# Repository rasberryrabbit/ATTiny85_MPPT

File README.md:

# ATTiny85
Solar MPPT circuit.
Fianally working first firmware, but it need more testing.
Button is calibrate op-amp offset voltage at no load. It stored EEPROM.

Coding by Arduino 1.8.7 / ATTinycore.
~Algorithm convert from old MPPT code of mine.~
It implement new simple algorithm that work well with high solar output.
~But it have low power output under low solar output condition(stuck in high voltage).~
It has no PWM noise at high load.(hopely)
It has 8KHz switching frequency.
It works better than old 16f676 or 12f675 version due to no PWM noise.

11 milli-ohm N-ch logic level FET(BUK9511) used for current sensor. 
It can replace by 11 mili-ohm or higher Rds-on(<40 milli) resistance logic level FET.

BUK9511-55A -> BUK9508-55A
Transistor 2N2222A -> BC547 or compatible
Transistor 2N2907A -> BC557 or compatible

L1 100~330uH

LM358N can replace by other pin-compatible regular OP-AMP.

D8-D9 used for 3.6v Reference. Each has about 1.8v voltage drop.

Q1 gate voltage is 3.6v. It's depend on FET specification.

Q1, Q2 can skip heat spreader with low POWER Solar panel. No heat with 10W panel.

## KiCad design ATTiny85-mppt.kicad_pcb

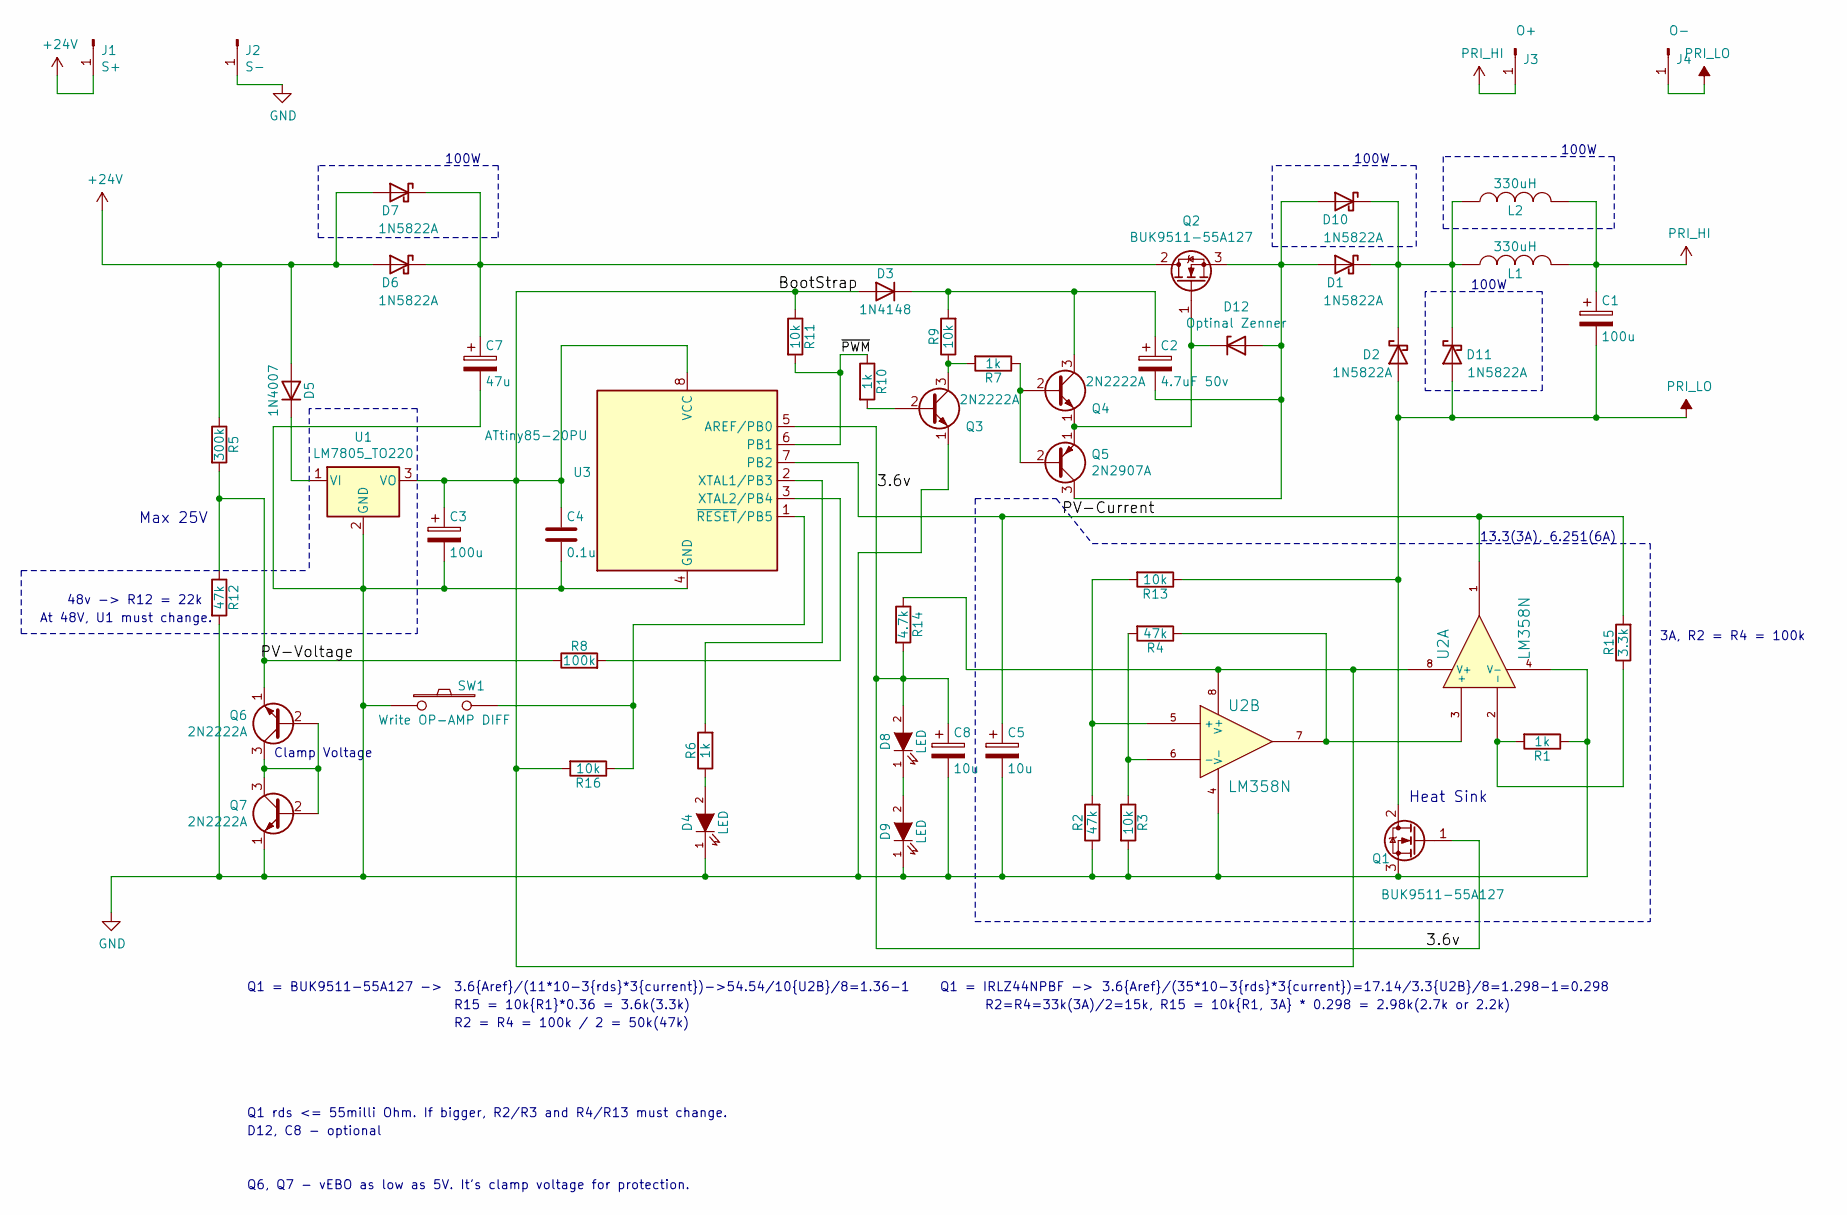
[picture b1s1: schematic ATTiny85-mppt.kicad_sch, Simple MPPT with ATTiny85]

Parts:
C1, C3: 100u; CP_Radial_D12.5mm_P5.00mm
C2: 4.7uF 50v; CP_Radial_D12.5mm_P5.00mm
C4: 0.1u; C_Disc_D12.5mm_W5.0mm_P7.50mm
C5, C8: 10u; CP_Radial_D12.5mm_P5.00mm
C7: 47u; CP_Radial_D12.5mm_P5.00mm
D1, D2, D6, D7, D10, D11: 1N5822A; D_DO-201AD_P15.24mm_Horizontal
D3: 1N4148; D_DO-41_SOD81_P10.16mm_Horizontal
D4, D8, D9: LED; LED_D4.0mm
D5: 1N4007; D_DO-41_SOD81_P10.16mm_Horizontal
D12: Optinal Zenner; D_DO-41_SOD81_P10.16mm_Horizontal
J1: S+; 1pin
J2: S-; 1pin
J3: O+; 1pin
J4: O-; 1pin
L1, L2: 330uH; L_Toroid_Vertical_L33.0mm_W17.8mm_P12.70mm_Pulse_KM-5
Q1, Q2: BUK9511-55A127; TO-220_Neutral123_Vertical
Q3, Q4, Q6, Q7: 2N2222A; TO-92_Inline_Wide
Q5: 2N2907A; TO-92_Inline_Wide
R1, R6, R7, R10: 1k; R_Axial_DIN0309_L9.0mm_D3.2mm_P12.70mm_Horizontal
R2, R4, R12: 47k; R_Axial_DIN0309_L9.0mm_D3.2mm_P12.70mm_Horizontal
R3, R9, R11, R13, R16: 10k; R_Axial_DIN0309_L9.0mm_D3.2mm_P12.70mm_Horizontal
R5: 300k; R_Axial_DIN0309_L9.0mm_D3.2mm_P12.70mm_Horizontal
R8: 100k; R_Axial_DIN0309_L9.0mm_D3.2mm_P12.70mm_Horizontal
R14: 4.7k; R_Axial_DIN0309_L9.0mm_D3.2mm_P12.70mm_Horizontal
R15: 3.3k; R_Axial_DIN0309_L9.0mm_D3.2mm_P12.70mm_Horizontal
SW1: Write OP-AMP DIFF; SW_PUSH_6mm
U1: LM7805_TO220; TO-220-3_Vertical
U2: LM358N; DIP-8_W7.62mm
U3: ATtiny85-20PU; DIP-8_W7.62mm

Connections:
+24V: D5.2 (A), D6.2 (A), D7.2 (A), J1.1, R5.1; also elsewhere on the board
/3.6v: C8.1, D8.2 (A), Q1.1 (G), R14.2, U3.5 (AREF/PB0)
/BootStrap: C3.1, C4.1, D3.2 (A), R11.1, R14.1, R16.2, U1.3 (VO), U2.8 (V+), U3.8 (VCC)
/PV-Current: C5.1, R15.2, U2.1, U3.7 (PB2)
/PV-Voltage: Q6.1 (E), R5.2, R8.1, R12.1
/~PWM: R10.1, R11.2, U3.6 (PB1)
GND: C3.2, C4.2, C5.2, C7.2, C8.2, D4.1 (K), D9.1 (K), J2.1, Q1.3 (S), Q3.1 (E), Q7.1 (E), R1.1, R2.1, R3.2, R12.2, SW1.1, U1.2 (GND), U2.4 (V-), U3.4 (GND); also elsewhere on the board
unnamed: C2.1, D3.1 (K), Q4.3 (C), R9.2
unnamed: C2.2, D1.2 (A), D10.2 (A), D12.2 (A), Q2.3 (S), Q5.3 (C)
unnamed: C7.1, D6.1 (K), D7.1 (K), Q2.2 (D)
unnamed: D1.1 (K), D2.1 (K), D10.1 (K), D11.1 (K), L1.1, L2.1
unnamed: D4.2 (A), R6.1
unnamed: D5.1 (K), U1.1 (VI)
unnamed: D8.1 (K), D9.2 (A)
unnamed: D12.1 (K), Q2.1 (G), Q4.1 (E), Q5.1 (E)
unnamed: Q3.2 (B), R10.2
unnamed: Q3.3 (C), R7.2, R9.1
unnamed: Q4.2 (B), Q5.2 (B), R7.1
unnamed: Q6.2 (B), Q6.3 (C), Q7.2 (B), Q7.3 (C)
unnamed: R1.2, R15.1, U2.2 (-)
unnamed: R3.1, R4.2, U2.6 (-)
unnamed: R4.1, U2.3 (+), U2.7
unnamed: R6.2, U3.2 (XTAL1/PB3)
unnamed: R8.2, U3.3 (XTAL2/PB4)
unnamed: R2.2, R13.2, U2.5 (+)
unnamed 25: R16.1, SW1.2, U3.1 (~RESET/PB5); also elsewhere on the board
PRI_HI: C1.1, J3.1, L1.2, L2.2; also elsewhere on the board
PRI_LO: C1.2, D2.2 (A), D11.2 (A), J4.1, Q1.2 (D), R13.1; also elsewhere on the board

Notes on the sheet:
3A, R2 = R4 = 100k
48v -> R12 = 22k
100W
3.6{Aref}/(11*10-3{rds}*3{current})->54.54/10{U2B}/8=1.36-1
Clamp Voltage
R2 = R4 = 100k / 2 = 50k(47k)
Heat Sink
D12, C8 - optional
Max 25V
At 48V, U1 must change.
13.3(3A), 6.251(6A)
Q1 = BUK9511-55A127 ->
Q1 rds <= 55milli Ohm. If bigger, R2/R3 and R4/R13 must change.
Q6, Q7 - vEBO as low as 5V. It's clamp voltage for protection.
R2=R4=33k(3A)/2=15k, R15 = 10k{R1, 3A} * 0.298 = 2.98k(2.7k or 2.2k)
Q1 = IRLZ44NPBF ->
R15 = 10k{R1}*0.36 = 3.6k(3.3k)
3.6{Aref}/(35*10-3{rds}*3{current})=17.14/3.3{U2B}/8=1.298-1=0.298

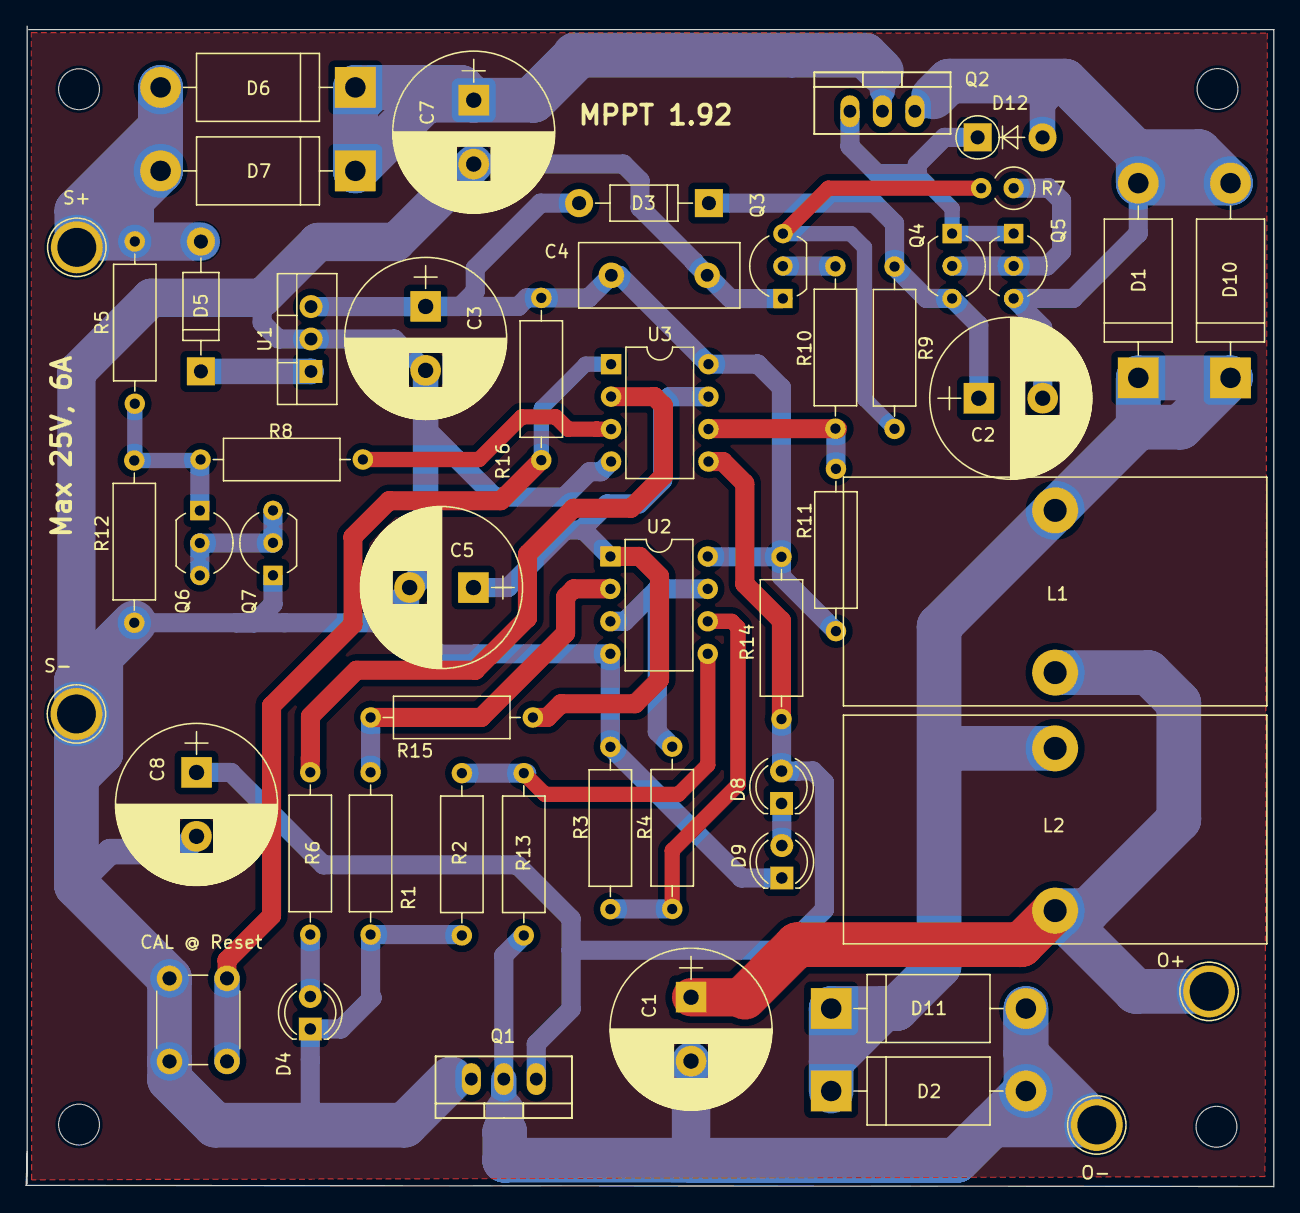
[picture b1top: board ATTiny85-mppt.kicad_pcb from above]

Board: 2 copper layers, 97.6 x 90.8 mm, 52 parts (0 on the bottom side), 28 nets.

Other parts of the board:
CAL @ Reset: Write OP-AMP DIFF; SW_PUSH_6mm
O+: O+; 1pin
O-: O-; 1pin
S+: S+; 1pin
S-: S-; 1pin

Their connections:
+24V: S+.1; also elsewhere on the board
GND: CAL @ Reset.1, S-.1; also elsewhere on the board
unnamed 25: CAL @ Reset.2; also elsewhere on the board
PRI_HI: O+.1; also elsewhere on the board
PRI_LO: O-.1; also elsewhere on the board

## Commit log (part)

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2018-10-21 First.
2018-10-21 update comment.
2018-10-24 fix pin mode on PWM.
2018-10-24 Fix pin Names. Fix delay values for 1MHz clock. Diable OCAL(OP-AMP Calibration) to default.
2018-10-24 Fix some settings.
2018-10-24 minor.
2018-10-24 Put some delays at start.
2018-10-25 Add hint for alternative FET IRLZ44.
2018-10-25 Add formula for OP-AMP Current Detector Value.
2018-10-26 Clarify alternative FET part number.
2018-10-26 Update more reliable value for FET IRLZ44N.
2018-10-28 fix OP-AMP formula.
2018-10-28 Update comment for bigger rds FET.
2018-10-30 Fix circuit - FET Bootstrap don't work. Fix code - Inverting mode PWM.
2018-10-30 fix typecast.
2018-10-30 remove stuck condition.
2018-10-30 Back to non-inverting. Fix FET Bootstrap.
2018-10-31 Fix by Invert Mode, 8Khz PWM. FET Bootstrap don't work with Higher frequency.
2018-10-31 Update PCB Layout.
2018-10-31 Update.
2018-10-31 Down PWM clock to 4KHz. ADC check test
2018-10-31 Fix _AnalogRead function.
2018-11-01 Fix ADC reference parameter. Fix OP-AMP Offset at first.
2018-11-01 fix FET bootstrap capacitor.
2018-11-01 update. but still don't work.
2018-11-01 Lower Max PWM.
2018-11-02 Add another P FET for switching.
2018-11-02 Refine code.
2018-11-02 add stall check. fix resetting parameters.
2018-11-02 miss one;
2018-11-03 Fix low voltage condition
2018-11-03 fix conditions.
2018-11-03 another condition.
2018-11-04 fix stall at low voltage.
2018-11-08 New method. WIP
2018-11-10 Add AREF capacitor.
2018-11-13 First working firmware. It need more testing.
2018-11-13 remove some component.
2018-11-13 regenerate pcb files.
2018-11-15 update readme.
2018-11-15 Increase ADC checking loop count.
2018-11-15 update bootstrap capacitor.
2018-11-17 update PCB file. update capacitor and add resistor.
2018-11-17 fix Q5 value.
2018-11-17 change bootstrap diode.
2018-11-18 clarify diode value.
2018-11-18 refine pcb layout.
2018-11-18 rearrnage some lines.
2018-11-18 rearrange.
2018-11-18 rearrange lines.
2018-11-19 lower adc loop.
2018-11-19 back to old adc loop.
2018-11-19 Don't be over optimal power voltage.
2018-11-20 update delay definitions.
2018-11-20 update delay constant. It may affect by ripple.
2018-11-20 upload image.
2018-11-22 Change update interval under current condition.
2018-11-22 Change min max PWM and test.
2018-11-23 update condition.
2018-11-23 update interval on low current.
2018-11-23 fix.
2018-11-24 stablize PWM.
2018-11-24 remove useless function and 8kHz PWM clock.
2018-11-25 add watchdog.
2018-11-25 add low current limit.
2018-11-25 check watchdog reset condition.
2018-11-25 R11 to 4.7k
2018-11-25 remove low current condition.
2018-11-26 avoid low voltage condition.
2018-11-27 fix led delay.
2018-11-27 sync adc reading.
2018-11-27 use non-interrupt handler for sync
2018-11-28 improve adc routine
2018-11-28 reduce adc loop.
2018-11-29 Remove R11. It is a lot lower current sensing voltage.
2018-11-29 Remove R11 on PCB layout.
2018-11-29 reduce update delay.
2018-11-30 Test adc sample times.
2018-11-30 disable edge detection. lower update delay.
2018-11-30 update PCB.
2018-11-30 update circuit.
2018-12-07 update C2 value. 10uF is also good.
2018-12-12 increase update interval. change ADC read order.
2018-12-13 fix current ADC reading. need more testing.
2018-12-13 set more optimized update interval.
2018-12-14 C6 to optional component.
2018-12-14 typecast on power multiple calc.
2018-12-15 Low voltage-High current stuck solved by removing C6. More testing.
2018-12-15 Reduce latency. It works on value 10.
2018-12-17 Remove C6
2018-12-17 Describe arduino tool option.
2018-12-18 Add alternative FET.
2018-12-20 R15 -> 4.7k. Current sensing is more higher than expected. 62mA -> 67mV.
2018-12-21 refine OP-AMP resistor formula. but it still same with first design(+10mV). it may safe under 3A current.
2018-12-22 update resistor formula.
2018-12-23 add note for R15.
2018-12-26 Add voltage clamp.
2019-01-07 fix low voltage(<2.7V) PLL lockup condition.
2019-01-22 another fix for low vcc stall.
2019-01-22 add delay time for PLL.
2019-01-31 Create LICENSE
2019-02-03 update watchdog init code.
2019-02-03 Change init order.
2019-02-04 reduce watchdog detection string size.
2019-02-04 watchdog code init at start.
2019-02-05 Back to old init order. BoD 2.7v is best for checking low voltage.
2019-02-06 make option PLL clock mode. Default to non-PLL clock for Timer1. It's unstable.
2019-02-06 Update circuit. Limit load when control circuit voltage is low.
2019-02-07 update code. no functional changes.
2019-02-08 Fix resistor values.
2019-02-13 Back to old circuit. Fix power-up high-z on at FET.
2019-02-13 back to old firmware.
2019-02-15 Change low PWM values for boot strap charging.
2019-02-15 Fix R1, R15 values.
2019-02-24 Update current sensing resistors.
2019-03-23 Add 48V input option.
2019-03-23 Add more comment.
2019-05-05 Disable Overflow check on PWM.
2019-05-06 Enable overflow checking. It has more stable output voltage.
2019-06-09 Remove low voltage protection code.
2021-07-11 C2 -> 4.7uF
2025-11-25 Fix circuit. R1 -> 1k.
2025-11-27 Update code.
2025-11-27 Fix PWM.
2025-11-28 Change BOD.
2025-11-28 Add High Fuse Hint.
2025-12-01 Update PCB files.
2025-12-01 Remove file.
2026-03-07 Reduce checking interval.
2026-03-10 Increase checking interval.
2026-03-10 Remove unused code.
2026-03-11 Check interval 18 to 19. Not much changes to output power. 18ms is most stable value.
2026-03-18 Revert checking interval to 18ms.
